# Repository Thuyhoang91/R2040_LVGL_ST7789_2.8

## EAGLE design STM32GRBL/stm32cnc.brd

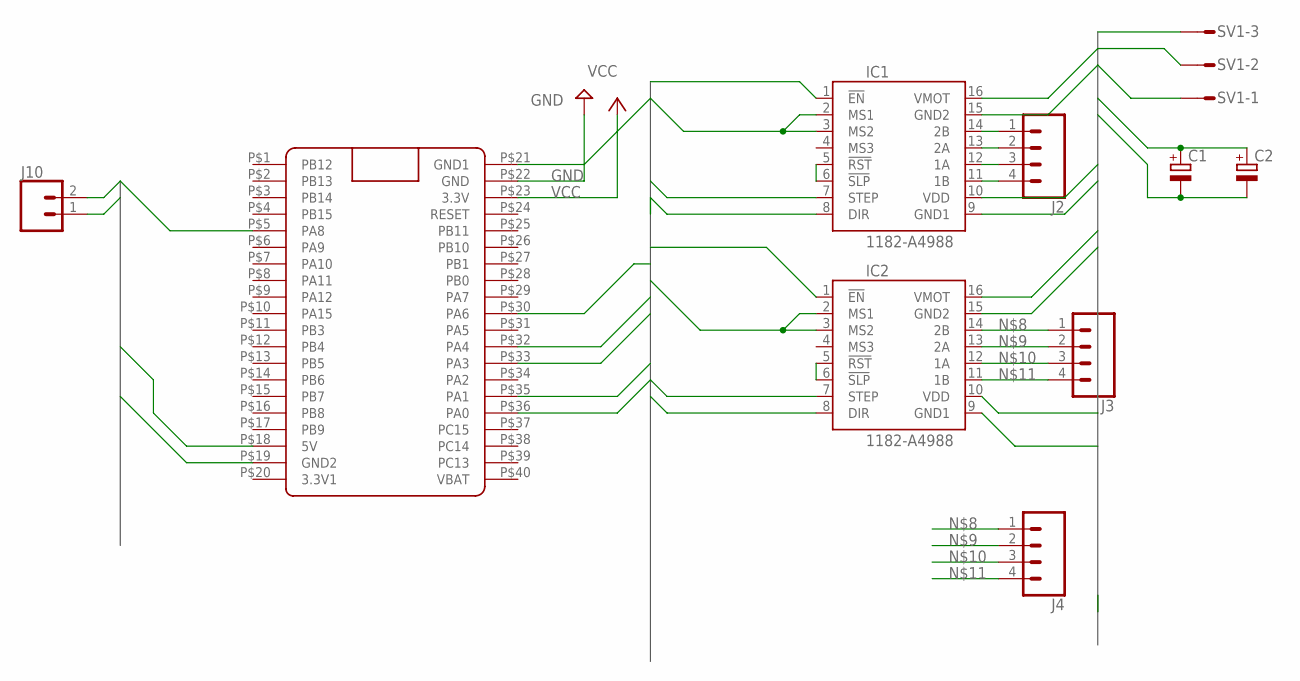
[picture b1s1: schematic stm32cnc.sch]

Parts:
C1, C2: CPOL-EUE2,5-6E; E2,5-6E
IC1, IC2: 1182-A4988; A4988
J2, J3, J4: CONN_04POLAR; MOLEX-1X4
J10: CONN_02POLAR; MOLEX-1X2
SV1: MT6-3
U$1: BLUE_PILL

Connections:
5-VCC: IC1.10 (VDD), IC2.10 (VDD), SV1.2, U$1.P$18 (5V)
12-VCC: C1.+, C2.+, IC1.16 (VMOT), IC2.16 (VMOT), SV1.3
EN: IC1.1 (!EN), IC2.1 (!EN), U$1.P$30 (PA6)
GND: C1.-, C2.-, IC1.9 (GND1), IC1.15 (GND2), IC2.9 (GND1), IC2.15 (GND2), J10.1, SV1.1, U$1.P$19 (GND2), U$1.P$21 (GND1), U$1.P$22 (GND)
unnamed: IC1.5 (!RST), IC1.6 (!SLP)
unnamed: IC2.5 (!RST), IC2.6 (!SLP)
unnamed: IC1.14 (2B), J2.1
unnamed: IC1.13 (2A), J2.2
unnamed: IC1.12 (1A), J2.3
unnamed: IC1.11 (1B), J2.4
unnamed: IC2.14 (2B), J3.1, J4.1
unnamed: IC2.13 (2A), J3.2, J4.2
unnamed: IC2.12 (1A), J3.3, J4.3
unnamed: IC2.11 (1B), J3.4, J4.4
PWM: J10.2, U$1.P$5 (PA8)
VCC: IC1.2 (MS1), IC1.3 (MS2), IC2.2 (MS1), IC2.3 (MS2), U$1.P$23 (3.3V)
X-DIR: IC1.8 (DIR), U$1.P$33 (PA3)
X-STEP: IC1.7 (STEP), U$1.P$36 (PA0)
Y-DIR: IC2.8 (DIR), U$1.P$32 (PA4)
Y-STEP: IC2.7 (STEP), U$1.P$35 (PA1)

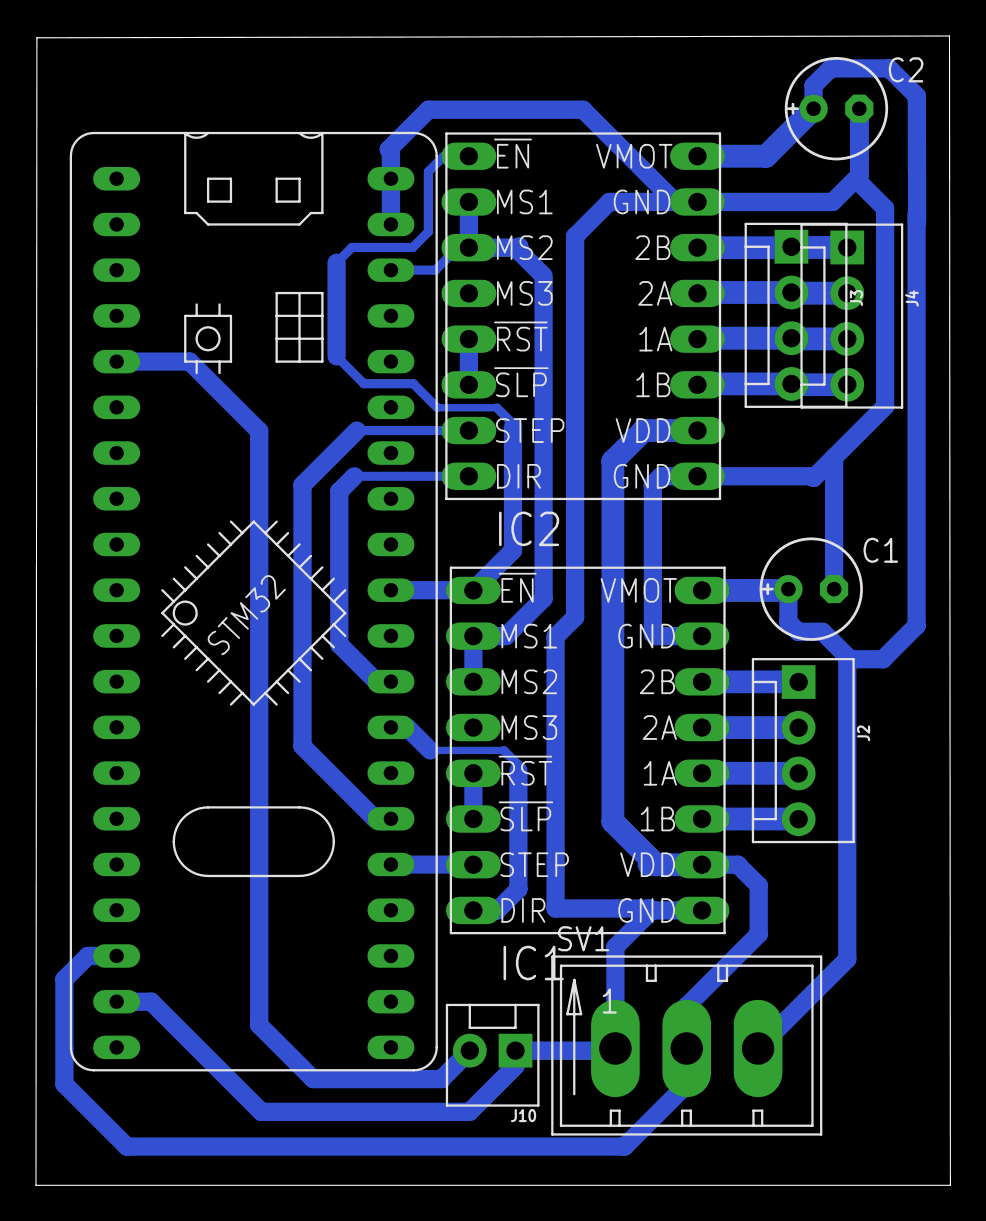
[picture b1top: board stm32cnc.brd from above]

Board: 2 copper layers, 50.8 x 63.9 mm, 10 parts (0 on the bottom side), 20 nets.

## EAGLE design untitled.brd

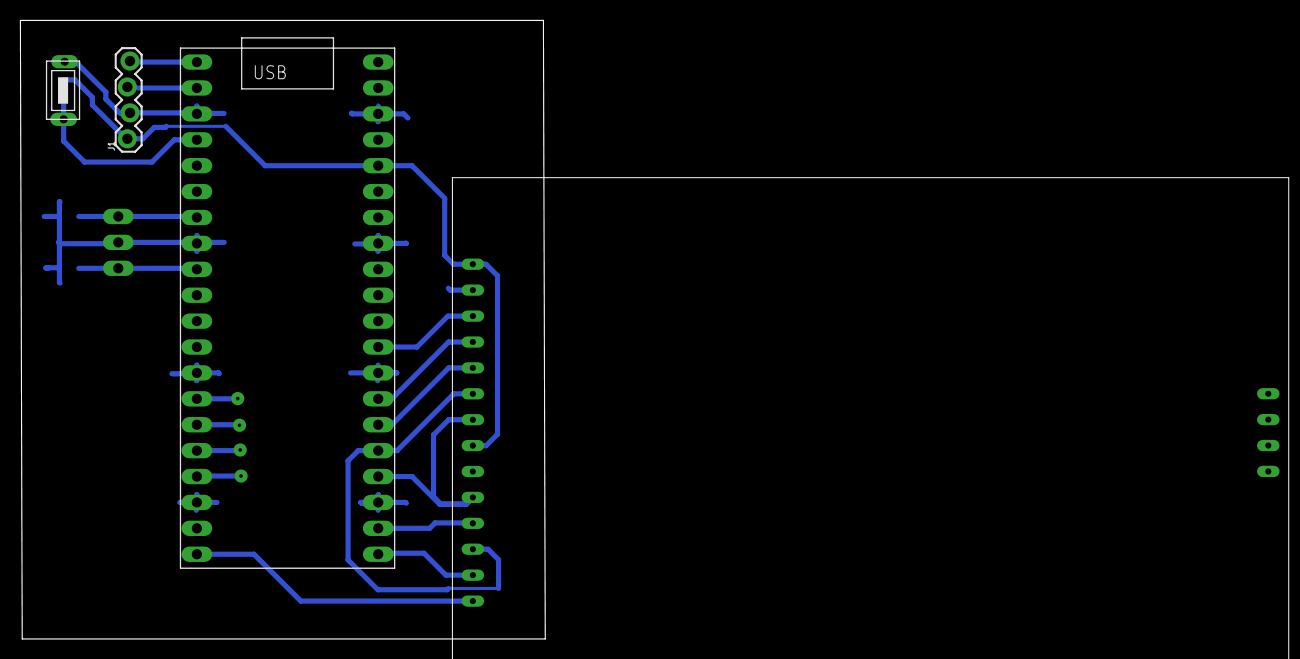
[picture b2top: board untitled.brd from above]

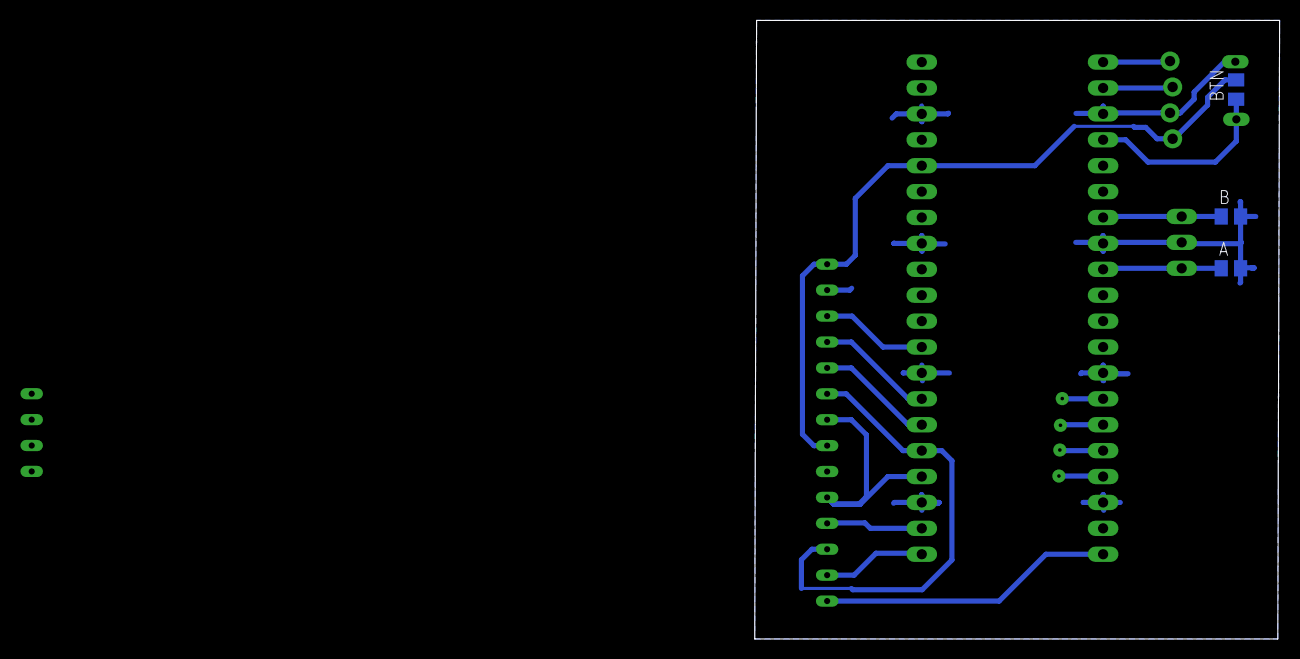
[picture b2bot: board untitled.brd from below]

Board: 2 copper layers, 51.5 x 60.7 mm, 8 parts (3 on the bottom side), 19 nets.

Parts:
A: M0805
B: M0805
BTN: M0805
J1: 1X04_LOCK
U$1: PICO; PICO_TH
U$2: RING_ENCODER; EC25-RING-ENCODER
U$3: ST7789; TFT-2.8-SD
U$4: 3X6X4.3-BUTTON; BTN-3X6X4.3

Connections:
3V3: BTN.2, J1.1, U$1.36, U$3.LED, U$3.VCC
A: A.1, U$1.9, U$2.A
B: B.1, U$1.7, U$2.B
BTN: BTN.1, U$1.4, U$4.P$1
D-CS: U$1.29, U$3.CS-DIS
D-DC: U$1.26, U$3.DC-DIS
D-RST: U$1.27, U$3.RES-DIS
GND: A.2, B.2, J1.2, U$1.3, U$1.8, U$1.13, U$1.18, U$1.23, U$1.28, U$1.33, U$1.38, U$2.C, U$3.GND, U$4.P$2
MISO: U$1.21, U$3.DO-T
MOSI: U$1.25, U$3.DI-T, U$3.MOSI-DIS
RX: J1.3, U$1.2
SCK: U$1.24, U$3.SCK-DIS, U$3.SCK-T
SD-CS: U$1.17, U$3.CS-SD
SD-MISO: U$1.16, U$3.MISO-SD
SD-MOSI: U$1.15, U$3.MOSI-SD
SD-SCK: U$1.14, U$3.SCK-SD
T-CS: U$1.22, U$3.CS-T
T-IRQ: U$1.20, U$3.IRQ-T
TX: J1.4, U$1.1

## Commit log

2025-09-06 Create code
2025-09-06 Rename code to code.c

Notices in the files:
parts and their libraries:
SparkFun-Connectors: Licensing: Creative Commons ShareAlike 4.0 International - https://creativecommons.org/licenses/by-sa/4.0
